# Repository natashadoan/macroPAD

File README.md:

# Natasha’s Sensory Fidget Macropad!

Here's my project: a 5-key fidget hackpad based off the starter project offered on highway. It was created as a way to learn to use Kicad and design hardware. Inside, there is a XIAO RP2040 microcontroller, 2 RGB LEDs whose colors can changes, and can be used as a stress/anxiety/boredom reliever or for functional keyboard shortcuts. The case is made of 2 parts: a bottom and a top, with the top having hole cutouts for the 5 keys.

This was my very first time using Kicad and designing a PCB, which was actually very fun! My friends and I go to artisan pop up markets in my hometown often, and I always see keypad fidget toys, so when I saw the beginner friendly project was a hackpad, I knew I had to attempt it.

---
## full 3D model of my project:

---

## schematic

---

## PCB layout:

---

## case design & assembly

---

## Bill of Materials (BOM)

- (1) XIAO PR2040 Microcontroller - https://www.seeedstudio.com/XIAO-RP2040-v1-0-p-5026.html ($3.99)
- (5) Tactile Switches - https://www.amazon.com/Momentary-Pushbutton-Switches-Breadboard-Electronic/dp/B09R3VZ5TN/ref=asc_df_B09R42NFGN?mcid=3442987eead832abb6c81ebd9b9579d4&hvocijid=10889451719894065161-B09R42NFGN-&hvexpln=73&tag=hyprod-20&linkCode=df0&hvadid=721245378154&hvpos=&hvnetw=g&hvrand=10889451719894065161&hvpone=&hvptwo=&hvqmt=&hvdev=c&hvdvcmdl=&hvlocint=&hvlocphy=9198292&hvtargid=pla-2281435178778&th=1 ($5.99)
- (2) SK6812MINI LEDs  - https://www.adafruit.com/product/3484 ($4.95)
- (1) PCB
- (4) 3mm Screws (securing the case) - https://www.amazon.com/M3-0-50-30mm-Stainless-Countersunk-MonsterBolts/dp/B078YWMP4R/ref=asc_df_B078YXQRYX?mcid=d6a2a29557ec310eb7b613e21eae92bd&hvocijid=14792519188918646431-B078YXQRYX-&hvexpln=73&tag=hyprod-20&linkCode=df0&hvadid=721245378154&hvpos=&hvnetw=g&hvrand=14792519188918646431&hvpone=&hvptwo=&hvqmt=&hvdev=c&hvdvcmdl=&hvlocint=&hvlocphy=9198292&hvtargid=pla-2281435176698&th=1 ($4.65)
 The case is 3D printed (top and bottom)

---

## other:
- this hackpad (and the code in git) is Python code (Circuit Python)- KMK

- future improvements - adding a dial, extra leds, more switches

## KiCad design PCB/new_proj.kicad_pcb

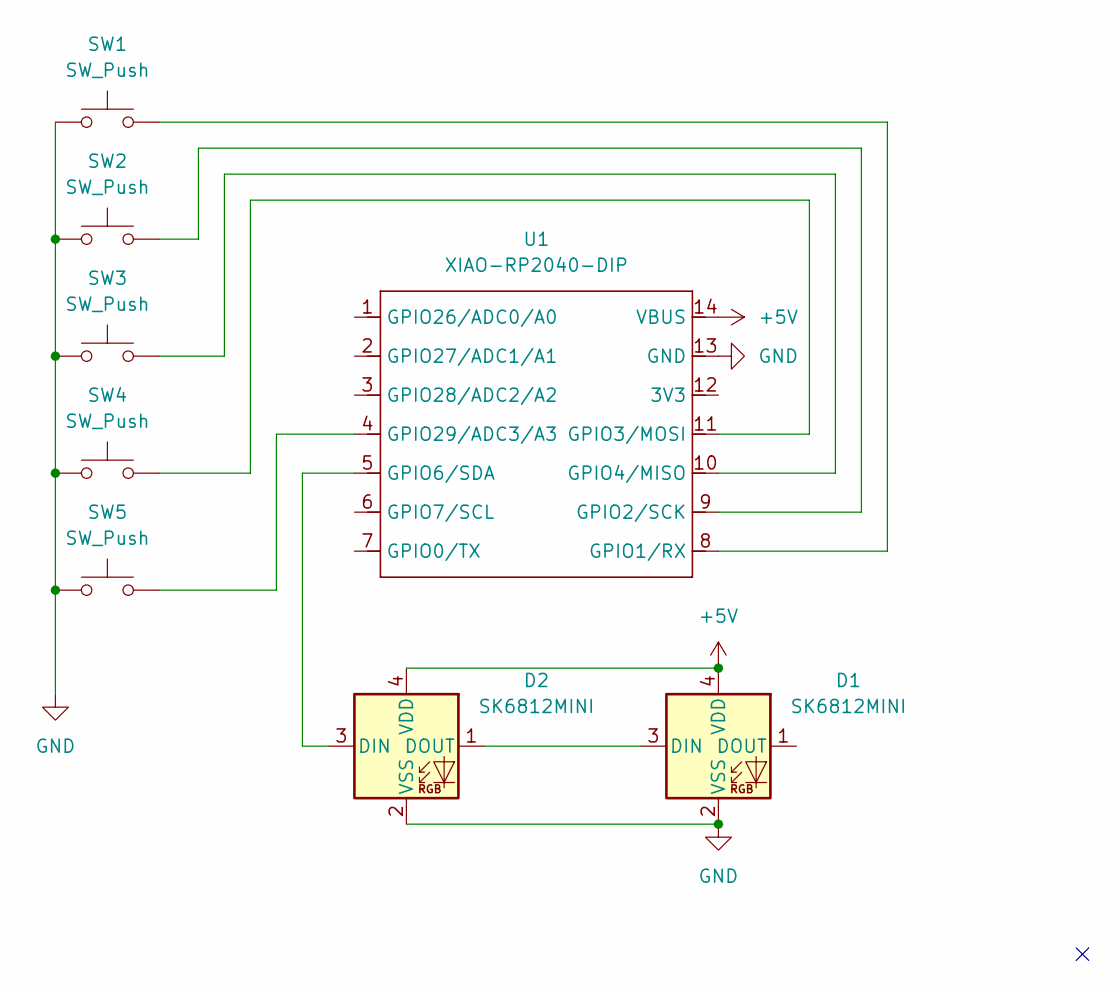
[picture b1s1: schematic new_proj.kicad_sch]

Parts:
D1, D2: SK6812MINI; LED_SK6812MINI_PLCC4_3.5x3.5mm_P1.75mm
SW1, SW2, SW3, SW4, SW5: SW_Push; SW_Cherry_MX_1.00u_PCB
U1: XIAO-RP2040-DIP

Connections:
+5V: D1.4 (VDD), D2.4 (VDD), U1.14 (VBUS)
GND: D1.2 (VSS), D2.2 (VSS), SW1.1, SW2.1, SW3.1, SW4.1, SW5.1, U1.13 (GND)
unnamed: D1.3 (DIN), D2.1 (DOUT)
unnamed: D2.3 (DIN), U1.5 (GPIO6/SDA)
unnamed: SW1.2, U1.8 (GPIO1/RX)
unnamed: SW2.2, U1.9 (GPIO2/SCK)
unnamed: SW4.2, U1.11 (GPIO3/MOSI)
unnamed: SW3.2, U1.10 (GPIO4/MISO)
unnamed: SW5.2, U1.4 (GPIO29/ADC3/A3)

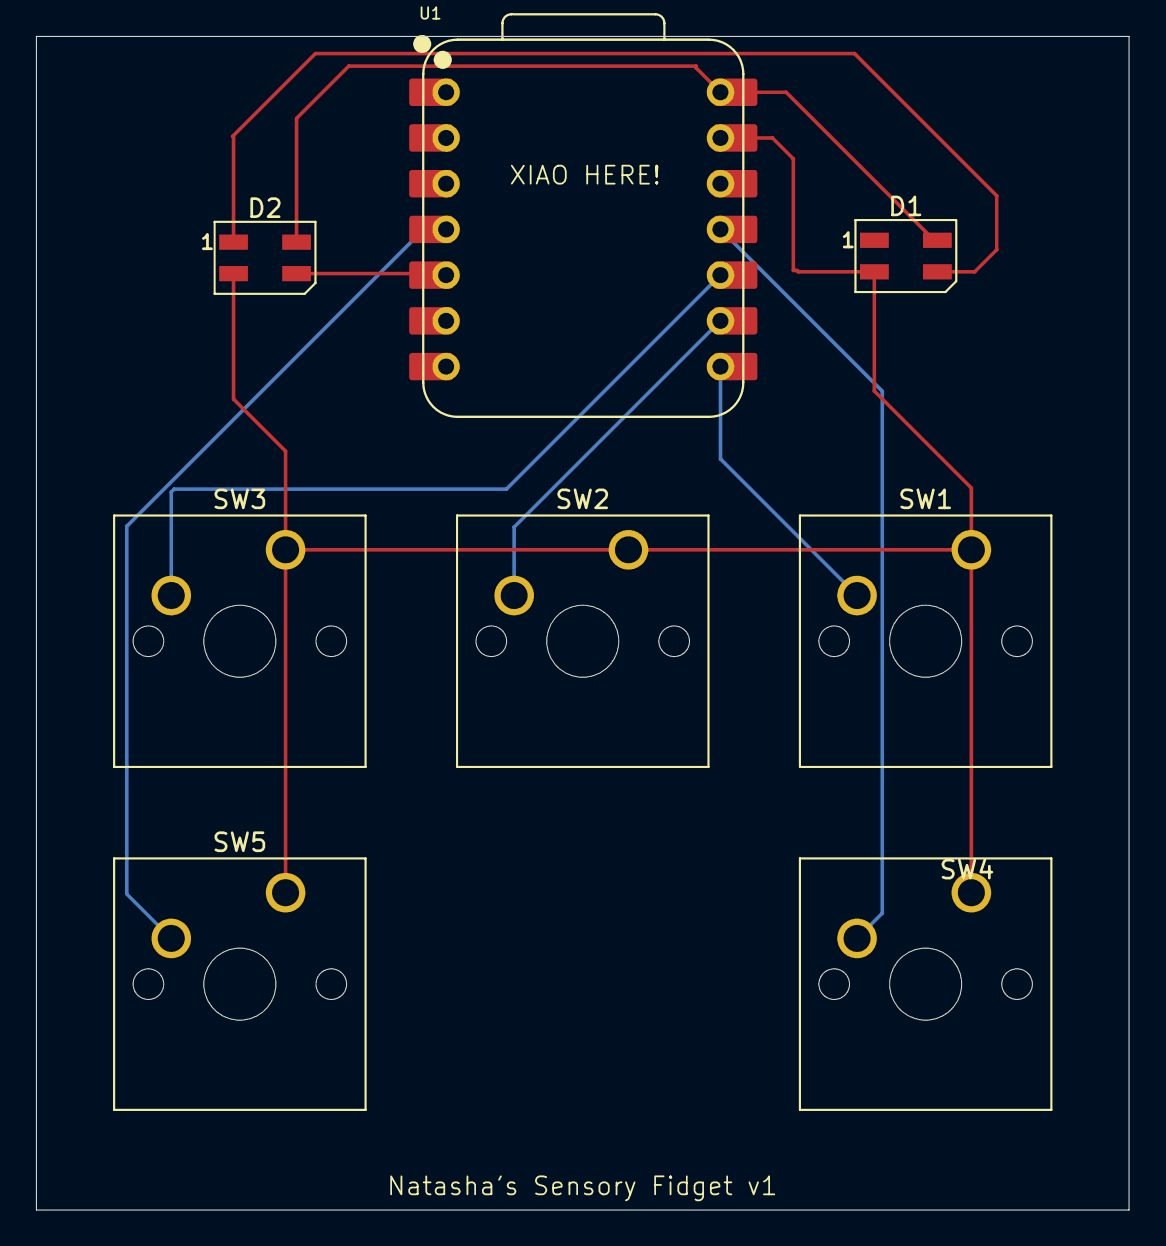
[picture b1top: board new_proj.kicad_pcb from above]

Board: 2 copper layers, 60.7 x 65.2 mm, 8 parts (0 on the bottom side), 9 nets.

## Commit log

2025-07-04 Initial commit with project files
2025-07-04 Update README.md
    first attempt
2025-07-04 new changes
2025-07-04 image change
2025-07-05 changing read me
2025-07-06 changed readME
2025-07-06 added link for screws
2025-07-06 added keys link
2025-07-06 fixed typos
2025-07-06 added prices
